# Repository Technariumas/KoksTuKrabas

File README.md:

# KoksTuKrabas
Installation for Lithuanian Sea museum

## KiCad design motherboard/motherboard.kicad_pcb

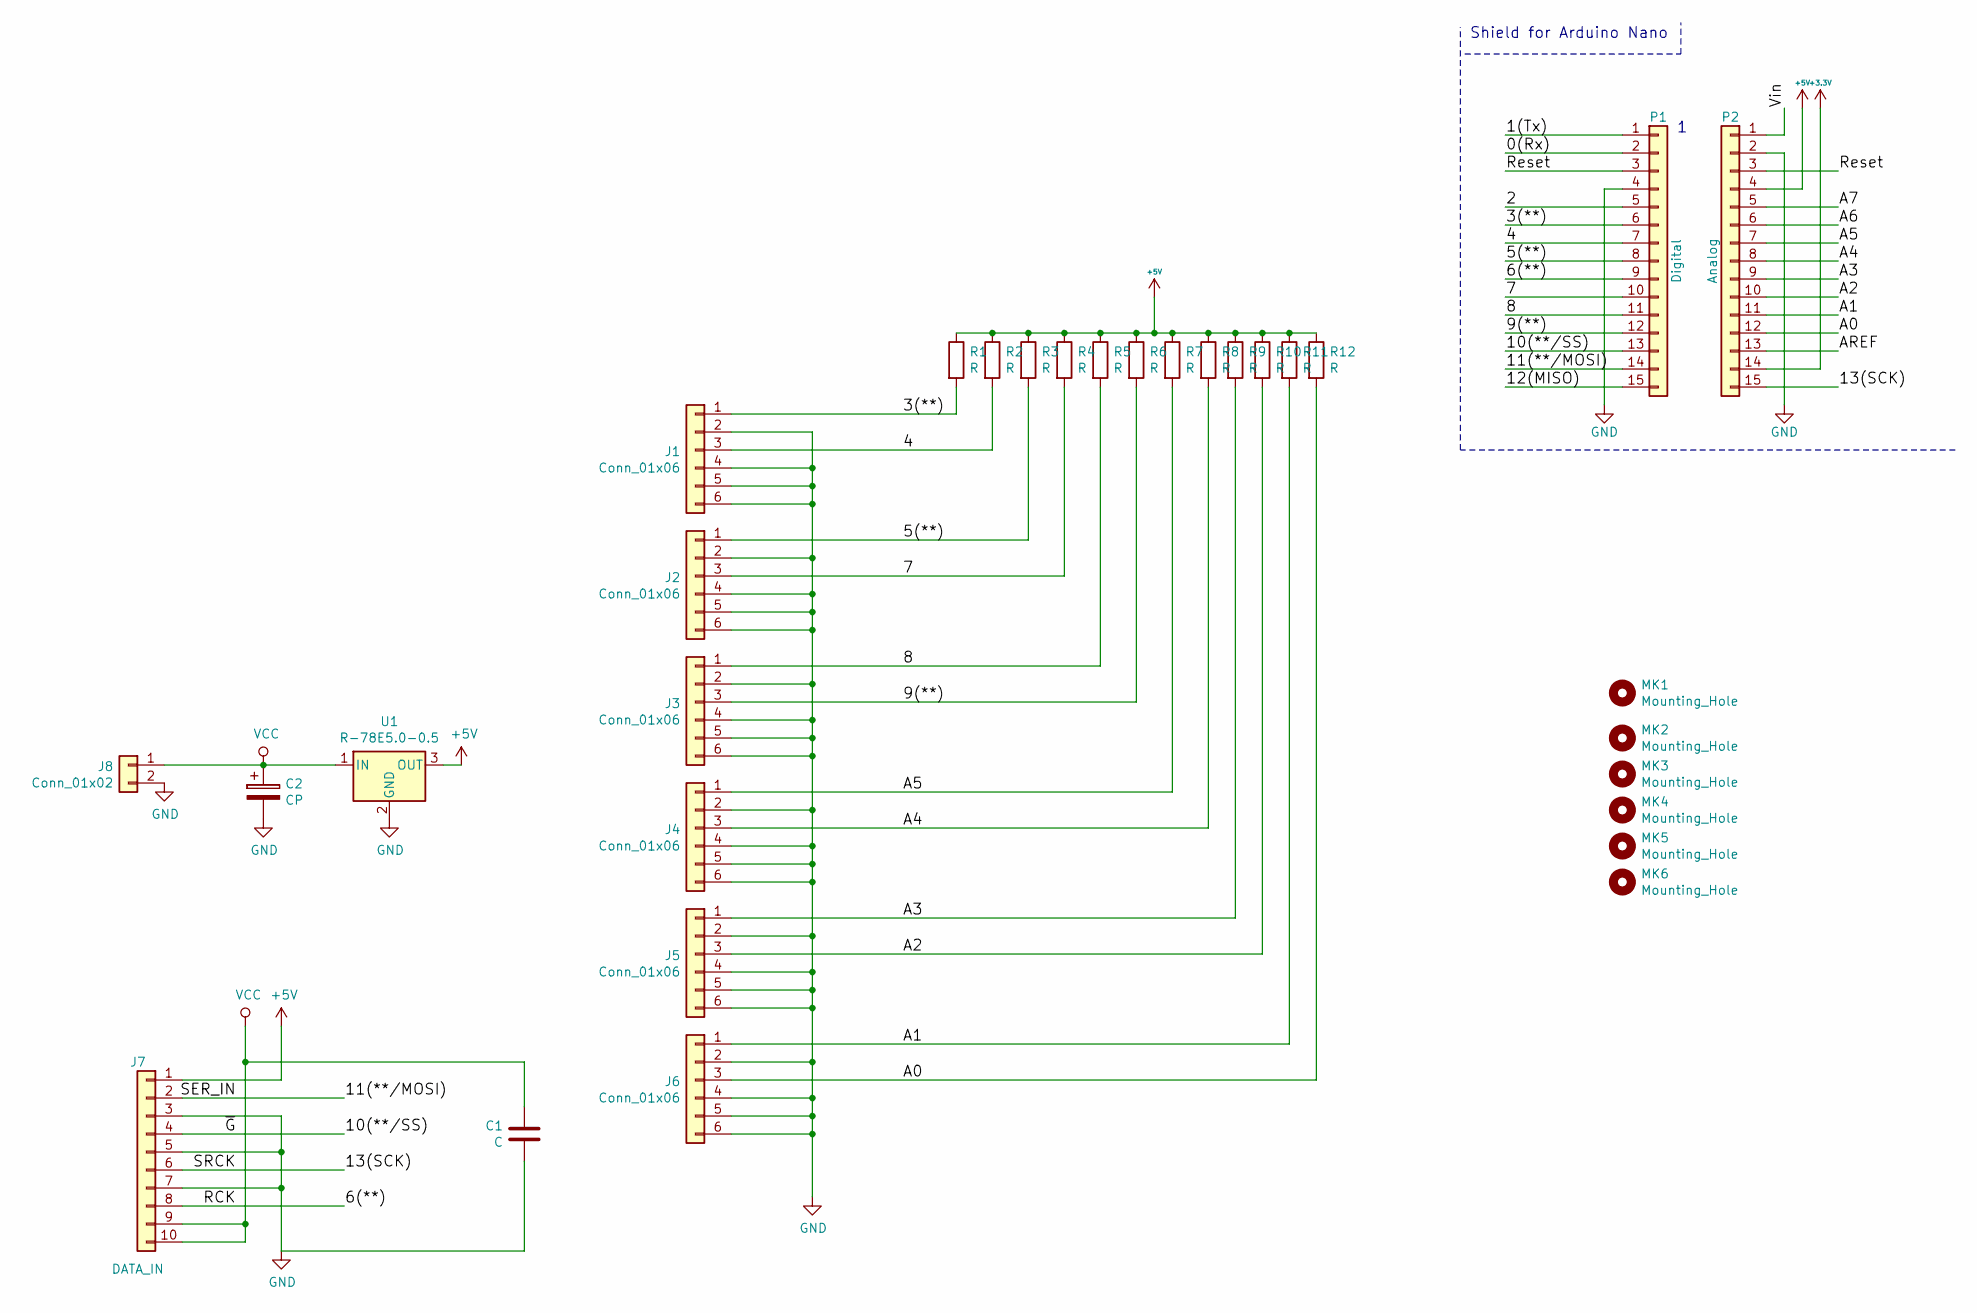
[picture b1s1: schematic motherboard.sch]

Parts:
C1: C; C_0805_HandSoldering; PartNo ?
C2: CP; CP_Radial_D13.0mm_P7.50mm; PartNo ?
J1, J2, J3, J4, J5, J6: Conn_01x06; IDC-Header_2x03_Pitch2.54mm_Straight; PartNo ?
J7: DATA_IN; IDC-Header_2x05_Pitch2.54mm_Straight; PartNo ?
J8: Conn_01x02; TerminalBlock_Phoenix_MKDS1.5-2pol; PartNo ?
MK1, MK2, MK3, MK4, MK5, MK6: Mounting_Hole; MountingHole_3.2mm_M3; PartNo ?
P1: Digital; Socket_Strip_Arduino_1x15; PartNo ?
P2: Analog; Socket_Strip_Arduino_1x15; PartNo ?
R1, R2, R3, R4, R5, R6, R7, R8, R9, R10, R11, R12: R; R_0805_HandSoldering; PartNo ?
U1: R-78E5.0-0.5; DCDC-Conv_RECOM_R-78E-0.5

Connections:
+3V3: P2.14
+5V: J7.1, P2.4, R1.1, R2.1, R3.1, R4.1, R5.1, R6.1, R7.1, R8.1, R9.1, R10.1, R11.1, R12.1, U1.3 (OUT)
/0(Rx): P1.2
/1(Tx): P1.1
/2: P1.5
/3(**): J1.1, P1.6, R1.2
/4: J1.3, P1.7, R2.2
/5(**): J2.1, P1.8, R3.2
/6(**): J7.8, P1.9
/7: J2.3, P1.10, R4.2
/8: J3.1, P1.11, R5.2
/9(**): J3.3, P1.12, R6.2
/10(**/SS): J7.4, P1.13
/11(**/MOSI): J7.2, P1.14
/12(MISO): P1.15
/13(SCK): J7.6, P2.15
/A0: J6.3, P2.12, R12.2
/A1: J6.1, P2.11, R11.2
/A2: J5.3, P2.10, R10.2
/A3: J5.1, P2.9, R9.2
/A4: J4.3, P2.8, R8.2
/A5: J4.1, P2.7, R7.2
/A6: P2.6
/A7: P2.5
/AREF: P2.13
/Reset: P1.3, P2.3
/Vin: P2.1
GND: C1.2, C2.2, J1.2, J1.4, J1.5, J1.6, J2.2, J2.4, J2.5, J2.6, J3.2, J3.4, J3.5, J3.6, J4.2, J4.4, J4.5, J4.6, J5.2, J5.4, J5.5, J5.6, J6.2, J6.4, J6.5, J6.6, J7.3, J7.5, J7.7, J8.2, P1.4, P2.2, U1.2 (GND)
VCC: C1.1, C2.1, J7.9, J7.10, J8.1, U1.1 (IN)

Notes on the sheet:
Shield for Arduino Nano

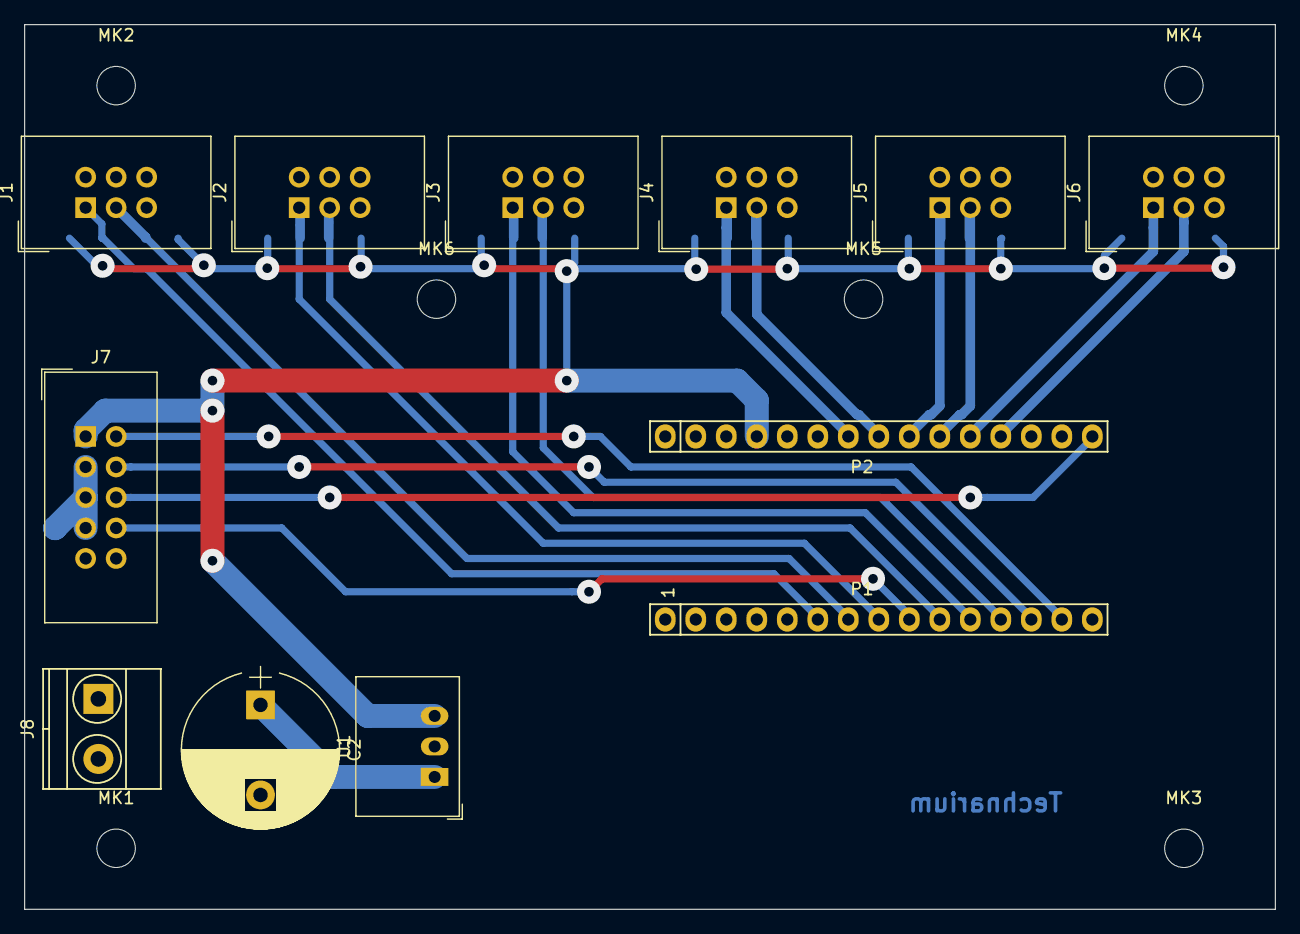
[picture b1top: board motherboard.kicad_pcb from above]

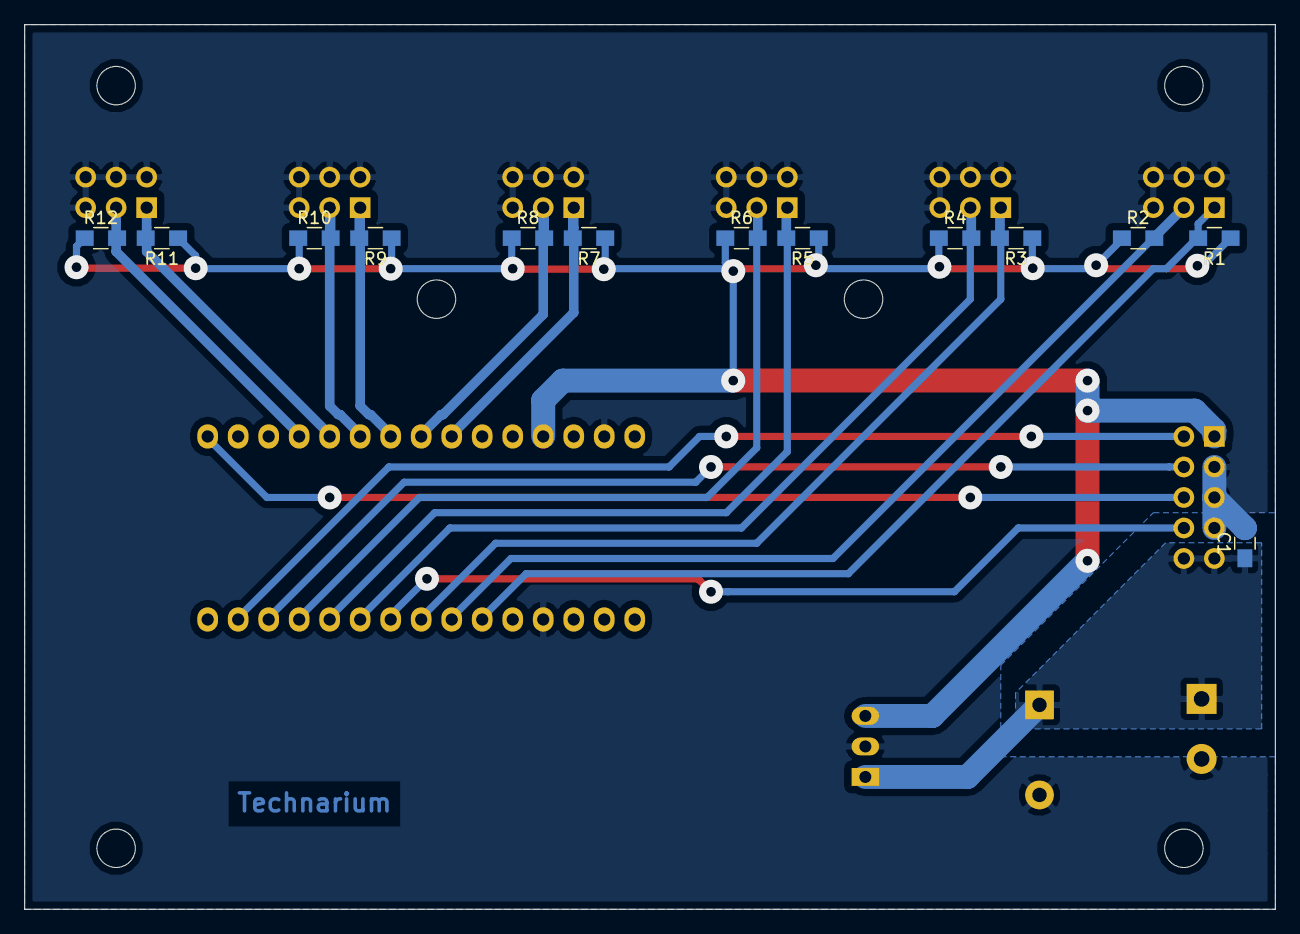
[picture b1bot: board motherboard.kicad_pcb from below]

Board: 2 copper layers, 104.1 x 73.7 mm, 31 parts (13 on the bottom side), 20 nets.

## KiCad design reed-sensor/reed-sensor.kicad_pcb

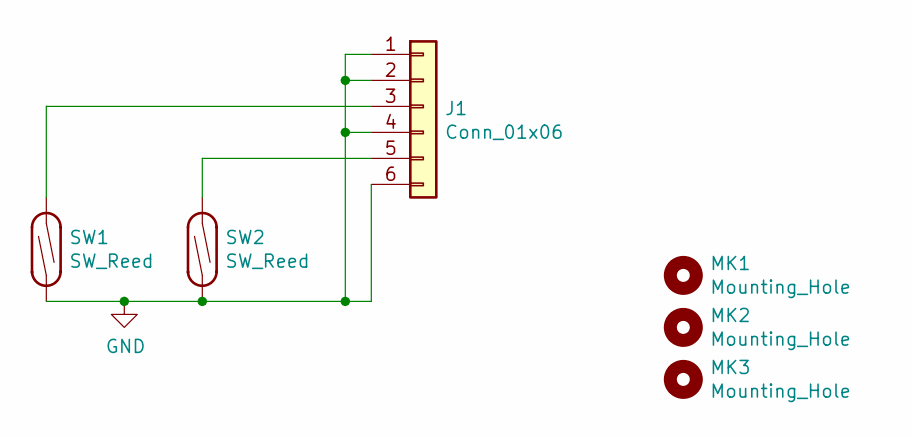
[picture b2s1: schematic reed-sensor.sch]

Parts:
J1: Conn_01x06; IDC-Header_2x03_Pitch2.54mm_Angled; PartNo ?
MK1, MK2, MK3: Mounting_Hole; MountingHole_3.2mm_M3; PartNo ?
SW1, SW2: SW_Reed; SOP100P1950X375-2N; PartNo ?

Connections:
GND: J1.1, J1.2, J1.4, J1.6, SW1.2, SW2.2
unnamed: J1.3, SW1.1
unnamed: J1.5, SW2.1

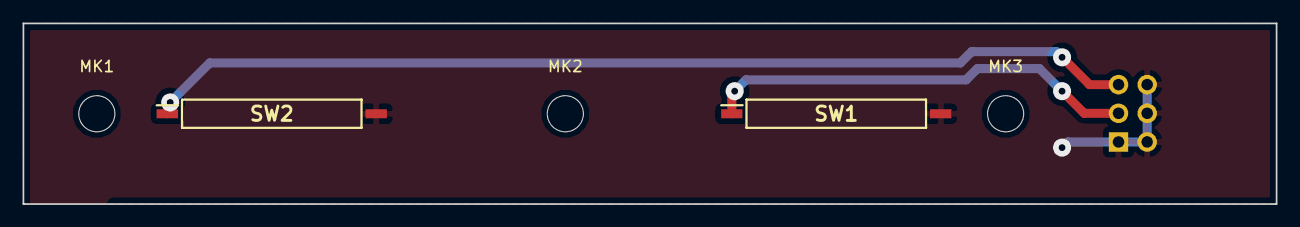
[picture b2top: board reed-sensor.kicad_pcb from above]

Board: 2 copper layers, 111.0 x 16.0 mm, 6 parts (1 on the bottom side), 3 nets.

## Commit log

2017-11-20 mockup
2017-11-20 Start working on reed sensor board
2017-11-20 Pareinam per visus bugnus ir patikrinam, kurio krabo savybe yra ant kiekvieno bugno, o ne tik ant pirmo. Du bitai - vienas bugnas
2017-11-20 Kintamąjame buf yra ne tik vieno būgno, bet visų būgnų būsena. Išsikeliame krabų skaitliukų ir buf inicializavimą iš analizės ciklo, procentus skaičiuojam paprasčiau, kaip reikės ant mažo MCU be floa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
2017-11-21 Add gerbers, order routing
2017-11-22 Crab calculations
2017-11-24 Add motherboard
2017-11-24 Add motherboard pics
2017-11-24 Add a 7-seg display test sketch
2017-11-26 Display segment pinout
2017-11-27 starting reed switch integration
2017-11-27 only one zero shown if percent == 0
2017-11-27 crab calculation and display separate
2017-11-27 working crab calculation, last zero
2017-11-30 corrected 1 display, crab value reindexing
2017-11-30 Add button functionality, add states, reset when play
2017-11-30 Add animation - numbers change gradually
